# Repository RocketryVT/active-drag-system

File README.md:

# Active Drag System (ADS)
This is the main codebase for Rocketry at Virginia Tech's Active Drag System, also known colloquially as the ADS, for the 2023-2024 competition year. It runs primarily on a Raspberry Pi Pico, and its goal is to autonomously control the ADS' deployment during flight.

`Eigen` Library, `cmake`, and `arm-none-eabi-gcc` tooling required for successful build.

## Clone

**Note: You must initialize the git submodules prior to utilizing CMake for a proper build.**

```shell
git clone https://github.com/RocketryVT/active-drag-system.git
cd active-drag-system/
git submodule update --init --recursive
```

## Build (Linux)
```shell
cmake -B build
cmake --build build
```
In the event that your preferred IDE has trouble locating header files and/or is displaying incorrect errors, pass ```-DCMAKE_EXPORT_COMPILE_COMMANDS=true``` to the first CMake command above. Similarly, if you wish to compile the additional tools (e.g. reading flash, calibrating the IMU, etc.), pass ```-DCOMPILE_TOOLS=true``` to the first CMake command above as well.

## Build (Windows)
Enable WSL2 in windows
Install Ubuntu 22 LTS from Windows Store
```shell
sudo apt update && upgrade
sudo apt install build-essential cmake gcc-arm-none-eabi
```
Then to actually build:
```shell
cmake -B build
cmake --build build
```

## Build Alternative (Mac)
```shell
brew install arm-none-eabi-gcc
```
To check if installed correctly run:
```shell
ls /opt/homebrew/bin | grep "none"
```
you should see a list including but not limited to:
```shell
arm-none-eabi-gcc
arm-none-eabi-g++
```
Next:
```shell
cmake -B build
cmake --build build
```

Binary files should be located in build/src/*.uf2 after a successful build.

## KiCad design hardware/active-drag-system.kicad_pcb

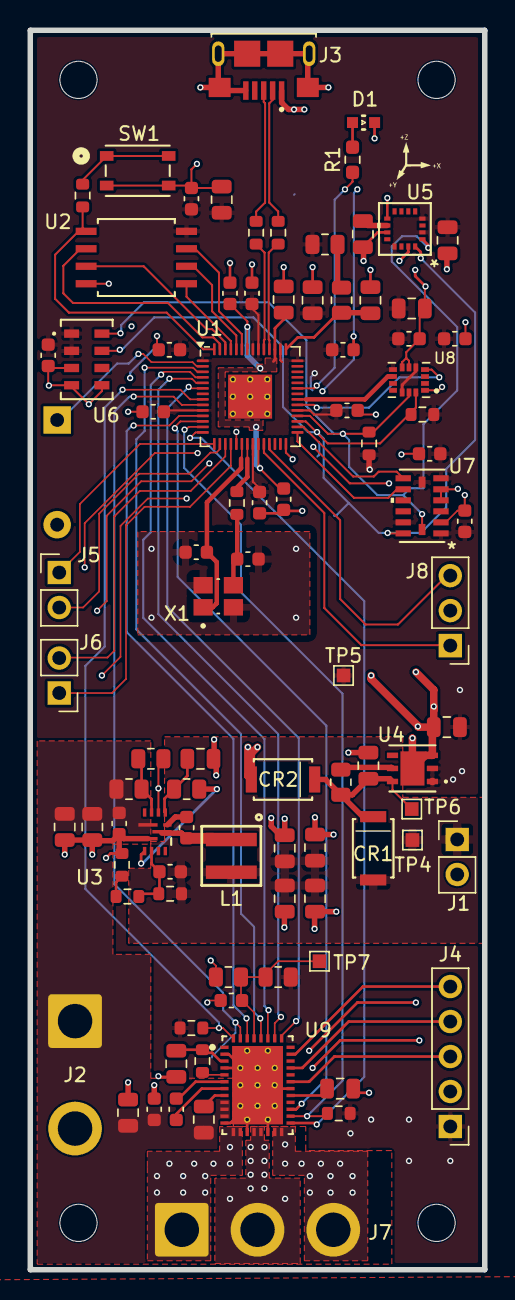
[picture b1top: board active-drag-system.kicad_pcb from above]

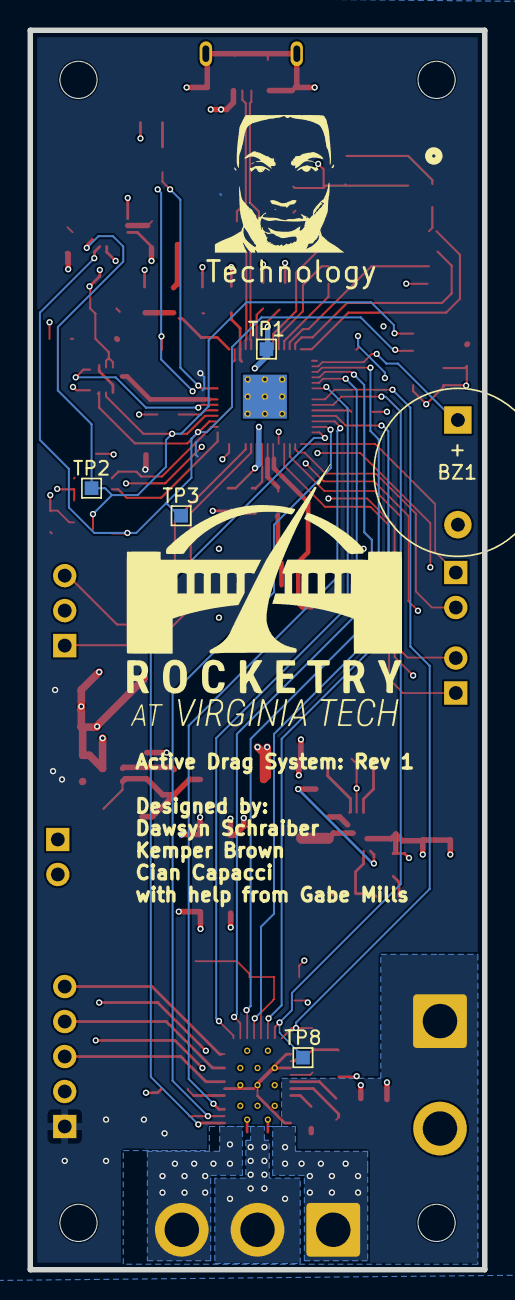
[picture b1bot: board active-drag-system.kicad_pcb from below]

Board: 4 copper layers, 33.0 x 90.0 mm, 99 parts (5 on the bottom side), 71 nets.

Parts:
BZ1: Buzzer; Buzzer_12x9.5RM7.6
C1, C2, C6, C7, C8, C9, C12, C14, C15, C16, C19, C28, C32, C33, C35, C36, C40: 100nF; C_0603_1608Metric
C3, C4, C5, C13, C34: 2.2uF; C_0805_2012Metric
C10, C11: 15pF; C_0603_1608Metric
C17, C18, C26, C27, C30, C37: 10uF; C_0805_2012Metric
C20, C21, C22, C23, C42: 22uF; C_0805_2012Metric
C24: 22pF; C_0603_1608Metric
C25, C29, C39, C41: 1uF; C_0805_2012Metric
C31: 10nF; C_0603_1608Metric
C38: 47nF; C_0603_1608Metric
CR1, CR2: PMEG3050EP_115; SDO_CFP5_SOD128_NEX
D1: WL-SMCW_0603
H1, H2, H3, H4: MountingHole; MountingHole_2.7mm_M2.5
J1, J5, J6: Conn_01x02_Pin; PinHeader_1x02_P2.54mm_Vertical
J2: Conn_01x02_Socket; SolderWire-2sqmm_1x02_P7.8mm_D2mm_OD3.9mm
J3: 10118193-0001LF; AMPHENOL_10118193-0001LF
J4: Conn_01x05_Pin; PinHeader_1x05_P2.54mm_Vertical
J7: Conn_01x03_Pin; SolderWire-2sqmm_1x03_P7.8mm_D2mm_OD3.9mm
J8: Conn_01x03_Pin; PinHeader_1x03_P2.54mm_Vertical
L1: WE-MAIA_4020
R1: 100; R_0603_1608Metric_Pad0.98x0.95mm_HandSolder
R2: 200; R_0805_2012Metric
R3, R4: 27; R_0603_1608Metric
R5, R6, R14, R15, R19, R21: 10k; R_0603_1608Metric
R7: 1; R_0805_2012Metric
R8, R9: 1k; R_0603_1608Metric
R10, R12, R13, R16, R18: 100k; R_0805_2012Metric
R11: 150k; R_0603_1608Metric
R17: 164k; R_0805_2012Metric
R20: 22; R_0603_1608Metric
SW1: PTS815 SJM 250 SMTR LFS; SW4_PTS815_SJM_250_SMTR_LFS_CNK
TP1: VCORE; TestPoint_Pad_1.0x1.0mm
TP2: SCL0; TestPoint_Pad_1.0x1.0mm
TP3: SDA0; TestPoint_Pad_1.0x1.0mm
TP4: 5V; TestPoint_Pad_1.0x1.0mm
TP5: 3V3; TestPoint_Pad_1.0x1.0mm
TP6: VSYS; TestPoint_Pad_1.0x1.0mm
TP7: ILIM; TestPoint_Pad_1.0x1.0mm
TP8: PWM; TestPoint_Pad_1.0x1.0mm
U1: RP2040; QFN-56-1EP_7x7mm_P0.4mm_EP3.2x3.2mm_ThermalVias
U2: W25Q128JVSIQ; SOIC_128JVSIQ_WIN
U3: TPS51386RJNR; VQFN-HR12_RJN_TEX
U4: LD39200PU33R; SON_DFN6_3X3_STM
U5: MMC5983MA; MMC5983MA_MEM
U6: MS560702BA03-50; SON8_MS5611_TEC
U7: ADXL375BCCZ; LGA_CC-14-1_ADI
U8: IIM-42653; PQFN50P250X300X97-14N
U9: MCT8316Z0RRGFR; RGF0040E-MFG
X1: ABM8AIG-12.000MHZ-12-2Z-T3; XTAL_ABM8AIG-12.000MHZ-12-2Z-T3

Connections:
+1V1: C2.1, C3.1, C15.1, TP1.1, U1.23 (DVDD), U1.45 (VREG_VOUT), U1.50 (DVDD)
/+3V3: C1.1, C4.1, C6.1, C7.1, C8.1, C9.1, C12.1, C13.1, C14.1, C27.1, C28.1, C29.2, C31.1, C32.1, C33.1, C34.1, C35.1, J4.1, R2.1, R5.1, R6.1, R17.2, R19.1, R21.1, TP5.1, U1.1 (IOVDD), U1.10 (IOVDD), U1.22 (IOVDD), U1.33 (IOVDD), U1.42 (IOVDD), U1.44 (VREG_IN), U1.48 (USB_VDD), U1.49 (IOVDD), U2.8 (VCC), U4.1 (OUT), U4.2 (ADJ/SENSE), U5.2 (VDD), U5.4 (SPI_CS), U5.13 (VDDIO), U6.1 (VDD), U6.2 (PS), U7.1 (VDD_I/O), U7.6 (VS), U7.7 (*CS), U7.12 (SDO/ALT_ADDRESS), U8.5 (VDDIO), U8.8 (VDD), U8.12 (AP_CS)
/+5V: C20.1, C21.1, C22.1, C23.1, C24.2, CR1.2, J1.1, L1.2, R11.2, TP4.1
/HG1: U1.30 (GPIO19), U7.8 (INT1)
/HG2: U1.29 (GPIO18), U7.9 (INT2)
/MAG: U1.28 (GPIO17), U5.15 (INT)
/MCU_RP2040/ADC_VREF: R2.2, R7.1
/MCU_RP2040/BRAKE: U1.11 (GPIO8), U9.38 (BRAKE)
/MCU_RP2040/BUZZ_OUT: BZ1.1 (+), U1.2 (GPIO0)
/MCU_RP2040/CLKOUT: U1.35 (GPIO23), U8.9 (INT2/FSYNC/CLKIN)
/MCU_RP2040/DRVOFF: U1.14 (GPIO11), U9.21 (DRVOFF)
/MCU_RP2040/FGOUT: R19.2, U1.8 (GPIO6), U9.40 (FGOUT)
/MCU_RP2040/I2C0_SCL: R5.2, TP2.1, U1.32 (GPIO21), U5.1 (SCL/SPI_SCK), U6.8 (SCLK), U7.14 (SCL/SCLK), U8.13 (AP_SCL/AP_SCLK)
/MCU_RP2040/I2C0_SDA: R6.2, TP3.1, U1.31 (GPIO20), U5.16 (SDA/SPI_SDI), U6.7 (SDI/SDA), U7.13 (SDA/SDI/SDIO), U8.14 (AP_SDA/AP_SDIO/AP_SDI)
/MCU_RP2040/I2C1_SCL: J6.1, U1.18 (GPIO15)
/MCU_RP2040/I2C1_SDA: J6.2, U1.17 (GPIO14)
/MCU_RP2040/LED_OUT: R1.1, U1.37 (GPIO25)
/MCU_RP2040/MOTOR_PWM: TP8.1, U1.9 (GPIO7), U9.39 (PWM)
/MCU_RP2040/QSPI_SCLK: U1.52 (QSPI_SCLK), U2.6 (CLK)
/MCU_RP2040/QSPI_SD0: U1.53 (QSPI_SD0), U2.5 (DI_(IO0))
/MCU_RP2040/QSPI_SD1: U1.55 (QSPI_SD1), U2.2 (DO_(IO1))
/MCU_RP2040/QSPI_SD2: U1.54 (QSPI_SD2), U2.3 (/WP_(IO2))
/MCU_RP2040/QSPI_SD3: U1.51 (QSPI_SD3), U2.7 (/HOLD_or_/RESET_(IO3))
/MCU_RP2040/QSPI_SS: R9.2, U1.56 (QSPI_SS), U2.1 (/CS)
/MCU_RP2040/SPI0_CSn0: U1.3 (GPIO1), U9.36 (nSCS)
/MCU_RP2040/SPI0_RX: U1.6 (GPIO4), U9.33 (SDO)
/MCU_RP2040/SPI0_SCK: U1.4 (GPIO2), U9.35 (SCLK)
/MCU_RP2040/SPI0_TX: U1.5 (GPIO3), U9.34 (SDI)
/MCU_RP2040/SWCLK: J8.1, U1.24 (SWCLK)
/MCU_RP2040/SWDIO: J8.3, U1.25 (SWD)
/MCU_RP2040/UART0_RX: J5.2, U1.16 (GPIO13)
/MCU_RP2040/UART0_TX: J5.1, U1.15 (GPIO12)
/MCU_RP2040/USB_D+: J3.3 (D+), R3.1
/MCU_RP2040/USB_D-: J3.2 (D-), R4.1
/MCU_RP2040/USB_DN: R4.2, U1.46 (USB_DM)
/MCU_RP2040/USB_DP: R3.2, U1.47 (USB_DP)
/MCU_RP2040/XIN: C10.1, U1.20 (XIN), X1.1
/MCU_RP2040/XOUT: R8.1, U1.21 (XOUT)
/MCU_RP2040/nFAULT: R21.2, U1.13 (GPIO10), U9.22 (nFAULT)
/MCU_RP2040/nSLEEP: U1.12 (GPIO9), U9.23 (nSLEEP)
/MG: U1.34 (GPIO22), U8.4 (INT1/INT)
/Motor Driver/HALL_SENSE_A: J4.3, U9.27 (HPA)
/Motor Driver/HALL_SENSE_B: J4.4, U9.29 (HPB)
/Motor Driver/HALL_SENSE_C: J4.5, U9.31 (HPC)
/Motor Driver/PHASE_A: J7.1, U9.13 (OUTA), U9.14 (OUTA)
/Motor Driver/PHASE_B: J7.2, U9.16 (OUTB), U9.17 (OUTB)
/Motor Driver/PHASE_C: J7.3, U9.19 (OUTC), U9.20 (OUTC)
/VBAT: C17.1, C18.1, C19.1, C36.1, C37.1, C39.1, J2.1, R10.1, U3.1 (VIN), U9.9 (VM), U9.10 (VM), U9.11 (VM)
/VBUS: CR2.2, J3.1 (VUSB)
GND: BZ1.2 (-), C1.2, C2.2, C3.2, C4.2, C5.2, C6.2, C7.2, C8.2, C9.2, C10.2, C11.2, C12.2, C13.2, C14.2, C15.2, C17.2, C18.2, C19.2, C20.2, C21.2, C22.2, C23.2, C25.2, C26.2, C27.2, C28.2, C29.1, C30.2, C31.2, C32.2, C33.2, C34.2, C35.2, C36.2, C37.2, C40.2, C41.1, C42.2, D1.1, J1.2, J2.2, J3.5 (GND), J3.S1 (SHIELD), J3.S2 (SHIELD__1), J3.S3 (SHIELD__2), J3.S4 (SHIELD__3), J3.S5 (SHIELD__4), J3.S6 (SHIELD__5), J4.2, J8.2, R12.2, R15.2, R18.2, SW1.3, SW1.4, U1.19 (TESTEN), U1.57 (GND), U2.4 (GND), U3.2 (PGND), U3.10 (AGND), U4.3 (GND), U4.7 (GND), U5.9 (GND), U5.11 (GND), U6.3 (GND), U6.4 (CSB), U6.5 (CSB), U7.2 (GND), U7.3 (RESERVED), U7.4 (GND), U7.5 (GND), U7.11 (RESERVED), U8.1 (AP_SDO/AP_AD0), U8.6 (GND), U8.7 (RESV), U9.2 (AGND), U9.4 (GND_BK), U9.12 (PGND), U9.15 (PGND), U9.18 (PGND), U9.26 (AGND), U9.41 (ThermalPad), X1.2 (GND), X1.4 (GND__1)
unnamed: C11.1, R8.2, X1.3
unnamed: D1.2, R1.2
unnamed: R9.1, SW1.1, SW1.2
unnamed: R14.2, R15.1
unnamed: C5.1, R7.2, U1.43 (ADC_AVDD)
unnamed: R10.2, R12.1, U3.11 (EN)
unnamed: C24.1, R11.1, R14.1, U3.4 (FB)
unnamed: R13.1, U3.3 (PG)
unnamed: C16.2, L1.1, U3.7 (SW)
unnamed: C16.1, U3.8 (VBST)
unnamed: C25.1, R13.2, U3.9 (VCC)
unnamed: R16.2, U4.5 (EN)
unnamed: C26.1, CR1.1, CR2.1, R16.1, TP6.1, U4.6 (IN)
unnamed: C30.1, U5.10 (CAP)
unnamed: C41.2, U9.25 (AVDD)
unnamed: C39.2, U9.8 (CP)
unnamed: C38.1, U9.7 (CPH)
unnamed: C38.2, U9.6 (CPL)
unnamed: C42.1, R20.2, U9.3 (FB_BK)
unnamed: C40.1, R17.1, R18.1, TP7.1, U9.37 (ILIM)
unnamed: R20.1, U9.5 (SW_BK)

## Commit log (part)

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2023-09-02 Project Structure and Build System
2023-09-15 Cross Compilation Process Ironed Out; Using Vagrant to standardize build process across distros/OSes, courtesy of ECE 3574
2023-10-14 added pru and base classes
2023-10-14 Update .gitignore ; remove unnecessary files
2023-10-28 updated files to do build to /out, currently can't get the gtest to build
2023-10-28 updated gitignore to keep only the build/out folder
2023-10-28 updated gitignore to only keep build/out folder
2023-10-28 Actually fixed cmake file for apple, remember that c and cxx compiler must be before project definition, added .ds_store to gitignore
2023-10-28 edited cmakelist to compile correctly on Windows WSL2/ Ubuntu, when using Clion or VSCode make sure to setup your CMake profiles correctly
2023-10-31 started implementing Boost::ASIO, unsure how to handle sensor data, global or passing struct around?; Need to read more about how ASIO works, wanted to commit so others can view
2023-11-10 Adding a 90% completed, compilable but untested ADS
2023-11-10 Made basic changes to actuator & sensor. Also added motor class
2023-11-10 Updated sensor & actuator classes, finished ads, added variable time step to kalman filter, set up all tests for future assertions
2023-11-11 Removed main.cpp
2023-11-11 Added more details to README
2023-11-12 Establishing header styles and naming conventions (snake_case) for source files; Build system up to main
2023-11-12 Revert "Header styles and file naming conventions"
2023-11-27 Changed some function parameters from pass-by-pointer to pass-by-reference. Also removed the std namespace
2023-11-27 Updated the .gitignore file
2023-11-27 Removed some files that should be gitignored
2024-01-01 Removed files that should be ignored
2024-01-02 Updated some test cases
2024-01-02 Removed test that should be ignored
2024-01-20 Up to date with Jazz's pull request
2024-02-19 Test Launch Branch Created; PRU Servo Control with Test Program
2024-02-21 Updated Logger functions to account for CSV format, and updated all files using the Logger functions.
2024-02-22 *Hypothetically* complete MPL implementation
    NEEDS HARDWARE TESTING
2024-02-23 IMU Header and init() method implementation
    Needs like, all data handling still lol
2024-02-23 We ball?
2024-03-25 Rearranged build so dependent upon cmake file already existing in pico-sdk; current executable prints current altitude, velocity, and time taken to read and calculate said values; ~320 us to do so
2024-04-02 Altimeter interrupt callback for Pad to Boost State; dummy templates for other callbacks with comments describing potential implementation details
2024-04-09 Established interrupt pins as pullup and active-low; adjusted callback functions to properly use function pointers; still need to verify interrupt system with vacuum chamber
2024-04-10 Removed weird artifact in .gitignore, adjust CMakeLists to auto pull pico sdk, added Dockerfile
2024-04-10 modified CMakeLists to auto pull sdk if not already downloaded, add build.sh script, fixed Dockerfile
2024-04-12 changed bno055 lin accel struct to use float instead of double
2024-04-12 added bno055 support not tested, but compiles, fixed CMakLists to before I messed with it
2024-04-13 Added Euler and aboslute linear accelration
2024-04-15 added base pwm functions and started on apogee detection
2024-04-15 State machine verified functional with logging capabilities; currently on same core
2024-04-17 Simple test program to see servo PWM range; logging with semaphores for safe multithreading
2024-04-18 Kalman filters generously provided from various sources for temporary replacement; minimum deployment 30 percent; state machine functionality restored; multithreading logging verified; altimeter brok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
2024-05-09 Various minimal changes; Flash size from 1MB to 8MB; M1939 to M2500T burn time; pin assignments for new PCB; External Status LED to Internal Status LED
2024-05-09 02/24/2024 Dalzell Test Launch Version (BB Black)
2024-05-09 Raspberry Pi Pico (#12)
    * Adding a 90% completed, compilable but untested ADS
    * Made basic changes to actuator & sensor. Also added motor class
    * Removed unnecessary .cpp files
    * Updated sensor & actuator classes, finished ads, added variable time step to kalman filter, set up all tests for future assertions
    * Relocated 'main' to 'active-drag-system.cpp'. Added more info to README
    * Removed main.cpp
2024-05-13 New Small Program to Aid in IMU Calibration; Essentially replicates functionality of Adafruit's CircuitPython script in C++
2024-06-09 Reintroducing in-house Kalman filter and removed external kalman filters, need to verify expectant behavior
2024-06-11 Added quaternion to euler angles conversion in IMU class
2024-06-12 Logging added back with now only logging when launch happens; heartbeat led; flash read to csv format
2024-06-13 Removed debug print statements; separated out general purpose buffer from altitude buffer for altimeter class
2024-06-13 imu_calib tool proper output formatting
2024-06-13 Where to begin…. (#13)
    +/- Reworked collection of altimeter related functions into altimeter class
    +/- Reworked bno055 class to be imu class with minimal functionality
    \- Removed external Kalman filter implementations in favor of own in house version
    \- Removed any/unused files
    \+ Added buffer logger for when sitting on pad for extended period of time in effort to prevent filling of flash chip
    \+ Added heartbeat LED for alive status
2024-09-28 Prototyping motor controller as tool prior to integrating with primary exec
2024-10-22 Initial commit to dev branch, added cmake flag for static library compilation (laptop was not happy about source compiling)
2024-10-24 Added header files for the 5 new sensors, no implementation yet
2024-10-29 Updated implementation for new baro initialization, has a really obnoxious bank of calibration values that need to be stored for conversion math
2024-12-08 Fixed broken class scopes in method definitions
2024-12-17 number something draft of ADS PCB, integrating with codebase for ease of access; removed low-G IMU and replaced with magnetometer; added buzzer; removed JSTs in favor of pads
2025-01-07 swapped power order of power reg and motor driver for better / edge connections
2025-01-08 Minimal design (aka w/o motor driver and added GPIO out); gerbers
2025-01-17 Removed bad GND connection to reserved pin on ADXL375 IMU; first error found in first batch
2025-01-23 Finished altimeter driver test implementation and minimal test drivers for mid and high-g IMUs; replaced low-g IMU with magnetometer; added test script with (functional) CMake build configuration for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
2025-02-01 update altimeter test tool for ms5607; board test tool in progress for more comprehensive pcb functionality verification; remove traces of pico W from main program to allow for compileability across 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
2025-02-07 Pick your poison: IIM-42653, MS-5607, ADXL375; board test with sensors in progress
2025-02-08 simple REPL for easy motor experimentation drop in
2025-02-09 Motor goes brrrrr
2025-02-16 working pwm; at very least up to 200 kHz
2025-02-16 Added comments on existing kalman_filter class implementation, pending rewrite to abstract out all designed matrices as constructor inputs
2025-02-17 PIO compiles, outputs nothing :(
2025-02-17 interrupt not blocking
2025-02-19 Swapped pulldown for pullup and tested pwm_measure to more closely match schem signal FGOUT
2025-02-19 added pwm_measure capability to motor_driver tool
2025-02-20 Implemented state extrapolation functions for orientation estimator, working on state update functions (need to finish deriving observation matrix)
2025-02-20 mct8316z driver
2025-02-20 it's all coming together
2025-02-21 In progress orientation_estimator update() method development, needs derivation of equivalent matrix R after frame transform of measurements
2025-03-02 Testing sections labeled to distinguish initialization commands
2025-03-11 Rev 2
2025-03-17 Implemented simple drivers for mag, imu, and accel; need to iron out a few kinks with inheritance specifiers on sensor_i2c class for helper methods and array syntax for [read_register_buffer()] calls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
2025-03-17 Various small refactors and fixes, ready for lab testing
2025-03-17 Unsuccessful first lab test, something is wrong with build system; can't get LED heartbeat on board or any USB device listing, but still works with other scripts
2025-03-17 Build system is fine, I am stupid and forgot to re-plug in the USB; something is hanging during the first initialize() call, will test soon to patch up
2025-03-19 SensorI2C implementation, in-progress refactoring of sensor drivers to use new class
2025-03-19 Reworked SensorI2C::write_buffer() to add a single byte to the TX buffer before dumping data buffer per Dawsyn's RTFM-ing
2025-03-19 version of pcb with no motor driver, only previously used servo enable and pwm circuit
2025-03-19 New Board Configuration File for Rev 2 of RP2040 Micro; Moved away from Pico_W architecture
2025-03-20 New altimeter class to support ms5607; heartbeat in include file now for ease of use; some cmake cleanup
2025-03-22 Kentucky Launch 03/22; Did NOT Deploy
2025-03-23 added basic freertos blinky, haven't tested but it compiles... def half the battle... also removed DS_Store hopefully, updated pico-sdk to 2.1.1
2025-03-23 updated eigen to lastest commit
2025-04-06 Initial work on cleaning up measurement testing - copied and repackaged contents of src/validate_peripherals.cpp into tools/measurement_test.cpp
2025-04-08 Reworked driver for Mid-G IMU, needs hardware testing to confirm unchanged functionality
2025-04-12 commands
2025-04-12 FreeRTOS introduction
2025-04-12 FreeRTOS repl and ms5607
2025-04-12 Rename to sensor names per gregory's request
2025-04-12 Bus arbitration change; iim42653 driver now formatted and simplified
2025-04-13 rename (again) to match magnetometer part num
2025-04-13 Need to figure out better way to pad log packets, THATS THE UNDERLYING ISSUE (pico_logger doesn't like 43 byte packets)
2025-04-15 Preliminary work on quaternion kalman filter implementation; needs further work for update/correct step and confirmation of prediction step calculations
2025-04-15 Full implementation of steps of filter process including NASTY observation Jacobian, needs implementations for quaternion/matrix operations but otherwise almost ready for testing
2025-04-17 Added verbose print statements in the section of pose estimation loop that a known calculation occurs to isolate which step it occurs at, hardware testing continuing shortly
2025-04-18 Normalized accel/mag values for orientation estimation purposes, filter output is now being processed correctly; beginning full math testing
2025-04-18 Filter is outputting but only sporadically converges still, seems to roughly find a value to float around briefly and then slides at an increasing rate; convergence rate much better with*out* gyro in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
2025-04-22 Events Handling for FreeRTOS
2025-04-22 In-progress testing changes, added temp debug print output during magnetometer calibration
2025-04-30 Added [scan] command to read_flash that scans both I2C buses for devices by performing dummy reads from pico sdk to test sensor breakout communication
2025-04-30 Initial commit, added blank driver for ICM20948; sensor is communicating successfully, beginning full implementation
2025-05-02 Working on implementing ICM20948 driver for magnetometer output; the way this chip is designed is actually mind-numbing, it has a whole separate internal I2C bus that you have to configure and untang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
2025-05-02 Bypassed internal itussy nonsense entirely, magnetometer now showing up as a separate device on bus; refactoring driver to have two separate devices to poll
2025-05-04 More driver work, partial implementation of mag data output from AK09916; needs complete implementation and hardware testing
2025-06-20 Fix16 imported with test operation
2025-06-20 IREC 2025
2025-06-20 Final ditch effort
2025-10-08 Fixed headers in log_format.hpp and active_drag_system.cpp to allow for WSL CMake compilation
2025-11-06 Add .gitignore
2025-11-28 Moved all submodules to the upper Avionics repo
2026-02-01 Updated CMakes to build correctly
2026-03-22 Copied in Jhamar's kalman filter port for further development
